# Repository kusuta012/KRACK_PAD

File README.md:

**Krackpad**

A custom 6-key macropad , designed as part of Hack Club's Blueprint program.

## IMAGES

Build 

Schematics

## PCB

## Front

## Back

## CAD

## bottom case

## top plate

## all together 

## BOM

- Seeed XIAO RP2040 × 1
- MX-style mechanical switches × 6
- Blank DSA keycaps (White) × 6
- M3 × 16 mm screws × 4
- M3 heat-set inserts × 4
- 3D printed case × 1

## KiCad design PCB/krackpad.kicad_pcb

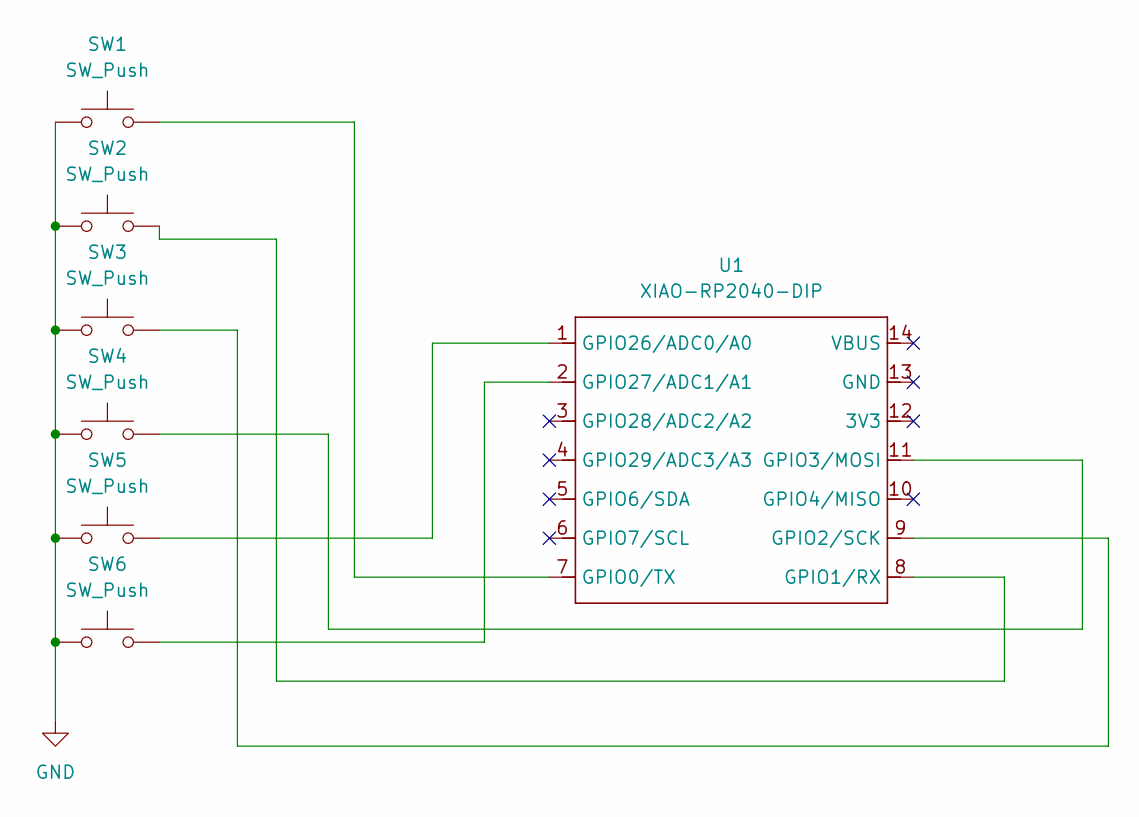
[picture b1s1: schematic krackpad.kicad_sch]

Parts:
SW1, SW2, SW3, SW4, SW5, SW6: SW_Push; SW_Cherry_MX_1.00u_PCB
U1: XIAO-RP2040-DIP

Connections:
GND: SW1.1, SW2.1, SW3.1, SW4.1, SW5.1, SW6.1
unnamed: SW1.2, U1.7 (GPIO0/TX)
unnamed: SW2.2, U1.8 (GPIO1/RX)
unnamed: SW3.2, U1.9 (GPIO2/SCK)
unnamed: SW4.2, U1.11 (GPIO3/MOSI)
unnamed: SW5.2, U1.1 (GPIO26/ADC0/A0)
unnamed: SW6.2, U1.2 (GPIO27/ADC1/A1)

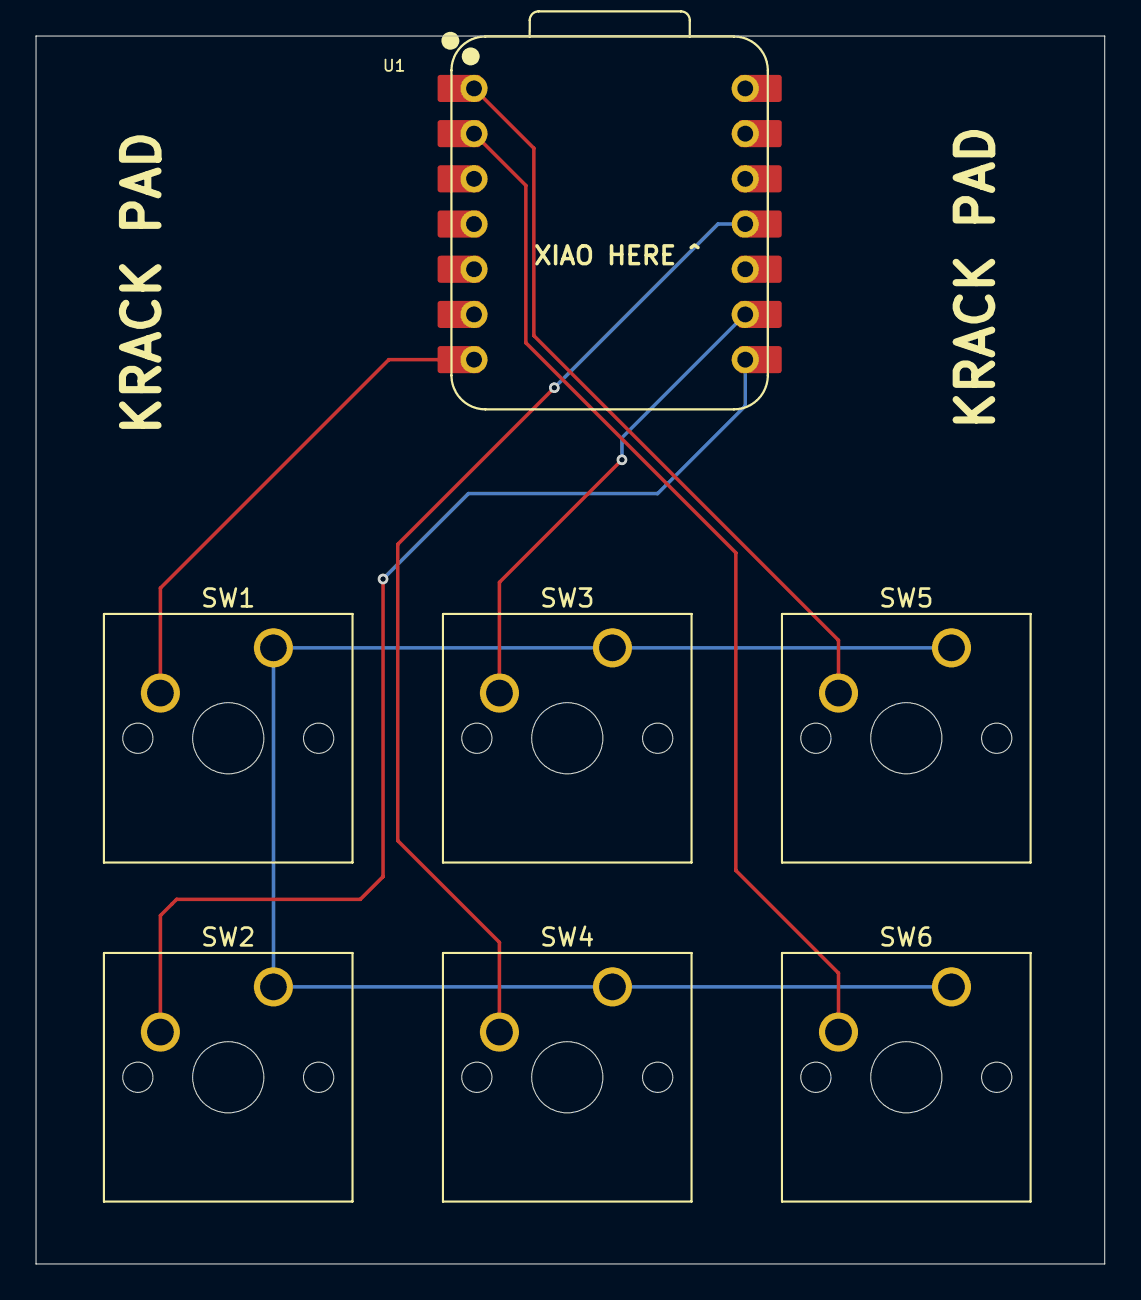
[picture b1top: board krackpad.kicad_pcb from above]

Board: 2 copper layers, 60.1 x 69.0 mm, 7 parts (0 on the bottom side), 7 nets.

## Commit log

2025-12-28 Revised
2025-12-28 Replace images in README.md
    Updated images in the README for bottom case and top plate sections.
2025-12-29 Add new section and image to README
2026-01-27 Add NeoPixel rainbow animation to keyboard firmware
2026-01-28 Update GPIO pin assignments for switches
2026-01-29 Enhance keyboard functionality with macros and setup
    Refactored keyboard setup and added macro definitions for various functions, including Git commands and system shortcuts.
2026-01-29 Update README with build image
    Added build image to README.
